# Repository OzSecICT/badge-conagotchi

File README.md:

# OzSec 2026: Conagotchi

Private repository for the OzSec 2026 Conagotchi badge — an ESP32-S3 interactive badge with a round GC9A01 display, virtual pet (Conagotchi) mode, and CTF challenge mode.

## Setup

Install host tools:

```bash
pip install esptool mpremote Pillow
```

## Flashing MicroPython firmware

```bash
esptool.py --chip esp32s3 --before default-reset --after hard-reset \
    write_flash -z 0x0 firmware/ESP32_GENERIC_S3-SPIRAM_OCT-20251209-v1.27.0.bin
```

## Deploying code

```bash
mpremote cp -r source/. :
mpremote reset
```

The VS Code default task (`Ctrl+Shift+B`) does both steps automatically.

## Converting images for the display

The GC9A01 display is 240×240 pixels round. Images must be converted from PNG to raw RGB565 binary before being copied to the badge — MicroPython cannot decode PNGs at runtime.

### Install the conversion tool dependency

```bash
pip install Pillow
```

### Full-screen backgrounds (240×240)

Design your PNG at 240×240 pixels. The corners outside the circular bezel are never shown, so no special treatment is needed — just design for a circle inscribed in the square.

```bash
python tools/convert_image.py your_image.png --outdir source/img
```

Produces `source/img/your_image.bin` — 115,200 bytes (240 × 240 × 2).

### Character animation frames

The Conagotchi idle animation uses sprite frames sized to the character bounding box (100×115 px by default). Export individual frames from your animation tool as transparent-background PNGs, then convert:

```bash
# Pre-sized PNGs (100×115) — convert without resizing
python tools/convert_image.py char_idle_0.png char_idle_1.png char_idle_2.png char_idle_3.png \
    --no-resize --outdir source/img

# OR crop from a full 240×240 mockup
python tools/convert_image.py mockup_frame0.png --crop 70,52,100,115 \
    --output source/img/char_idle_0.bin
```

The `--crop` coordinates (`x,y,w,h`) match the `_CHAR_X`, `_CHAR_Y`, `_CHAR_W`, `_CHAR_H` constants in `source/screens/conagotchi.py`.

### Menu button sprites

Each navigation button has three states: unselected (baked into the background), selected, and pressed. The selected/pressed states are small sprite files:

```bash
# Pre-sized sprite PNG
python tools/convert_image.py btn_pet_sel.png --no-resize --outdir source/img

# OR crop the button region from a full 240×240 state mockup
# Coordinates match the _BUTTONS table in source/screens/menu.py
python tools/convert_image.py menu_mockup_selected.png --crop 90,5,60,45 \
    --output source/img/btn_pet_sel.bin
```

### Compositing transparent overlays

If your overlay PNG has an alpha channel (transparency), composite it onto the background before converting:

```bash
python tools/convert_image.py background.png overlay.png \
    --composite --output source/img/result.bin
```

### Deploy images to badge

Images live in `source/img/` and are deployed alongside the Python files:

```bash
mpremote cp -r source/. :
```

### Expected image files

| File | Purpose |
|------|---------|
| `source/img/logo.bin` | Splash screen background |
| `source/img/{character}/background.bin` | Per-character main screen background (240×240) |
| `source/img/{character}/character.bin` | Idle animation base frame (80×80) |
| `source/img/{character}/idle_1.bin` … | Additional idle animation frames (optional) |
| `source/img/menu_bg.bin` | Menu screen background (all buttons unselected) |
| `source/img/btn_{id}_sel.bin` | Per-button selected state sprite |
| `source/img/btn_{id}_press.bin` | Per-button pressed state sprite |

The active character is set by `_CHARACTER` in `source/screens/conagotchi.py` (currently `"hackachi"`).

All `.bin` files are gitignored — generate them locally from your source PNGs.

## Hardware notes

- IR receiver to be changed to TSOP57438TT1 ([JLCPCB part](https://jlcpcb.com/partdetail/VishayIntertech-TSOP57438TT1/C3742825))

## Diagnostics

Run this on the REPL to check memory and flash:

```python
import gc, sys, esp32, os; gc.collect(); print(f"\n=== MicroPython Info ===\nImplementation: {sys.implementation}\nPlatform: {sys.platform}\nuname: {os.uname()}\n\n=== Memory ===\nFree: {gc.mem_free()/1024:.1f} KB\nUsed: {gc.mem_alloc()/1024:.1f} KB\nTotal: {(gc.mem_free()+gc.mem_alloc())/1024:.1f} KB\n\n=== Heap Regions ==="); [print(f"  {r[0]/1024/1024:.2f} MB total, {r[1]/1024/1024:.2f} MB free, {r[2]} largest block") for r in esp32.idf_heap_info(esp32.HEAP_DATA)]; print(f"\n=== Flash ==="); import esp; print(f"  Flash size: {esp.flash_size()/1024/1024:.0f} MB")
```

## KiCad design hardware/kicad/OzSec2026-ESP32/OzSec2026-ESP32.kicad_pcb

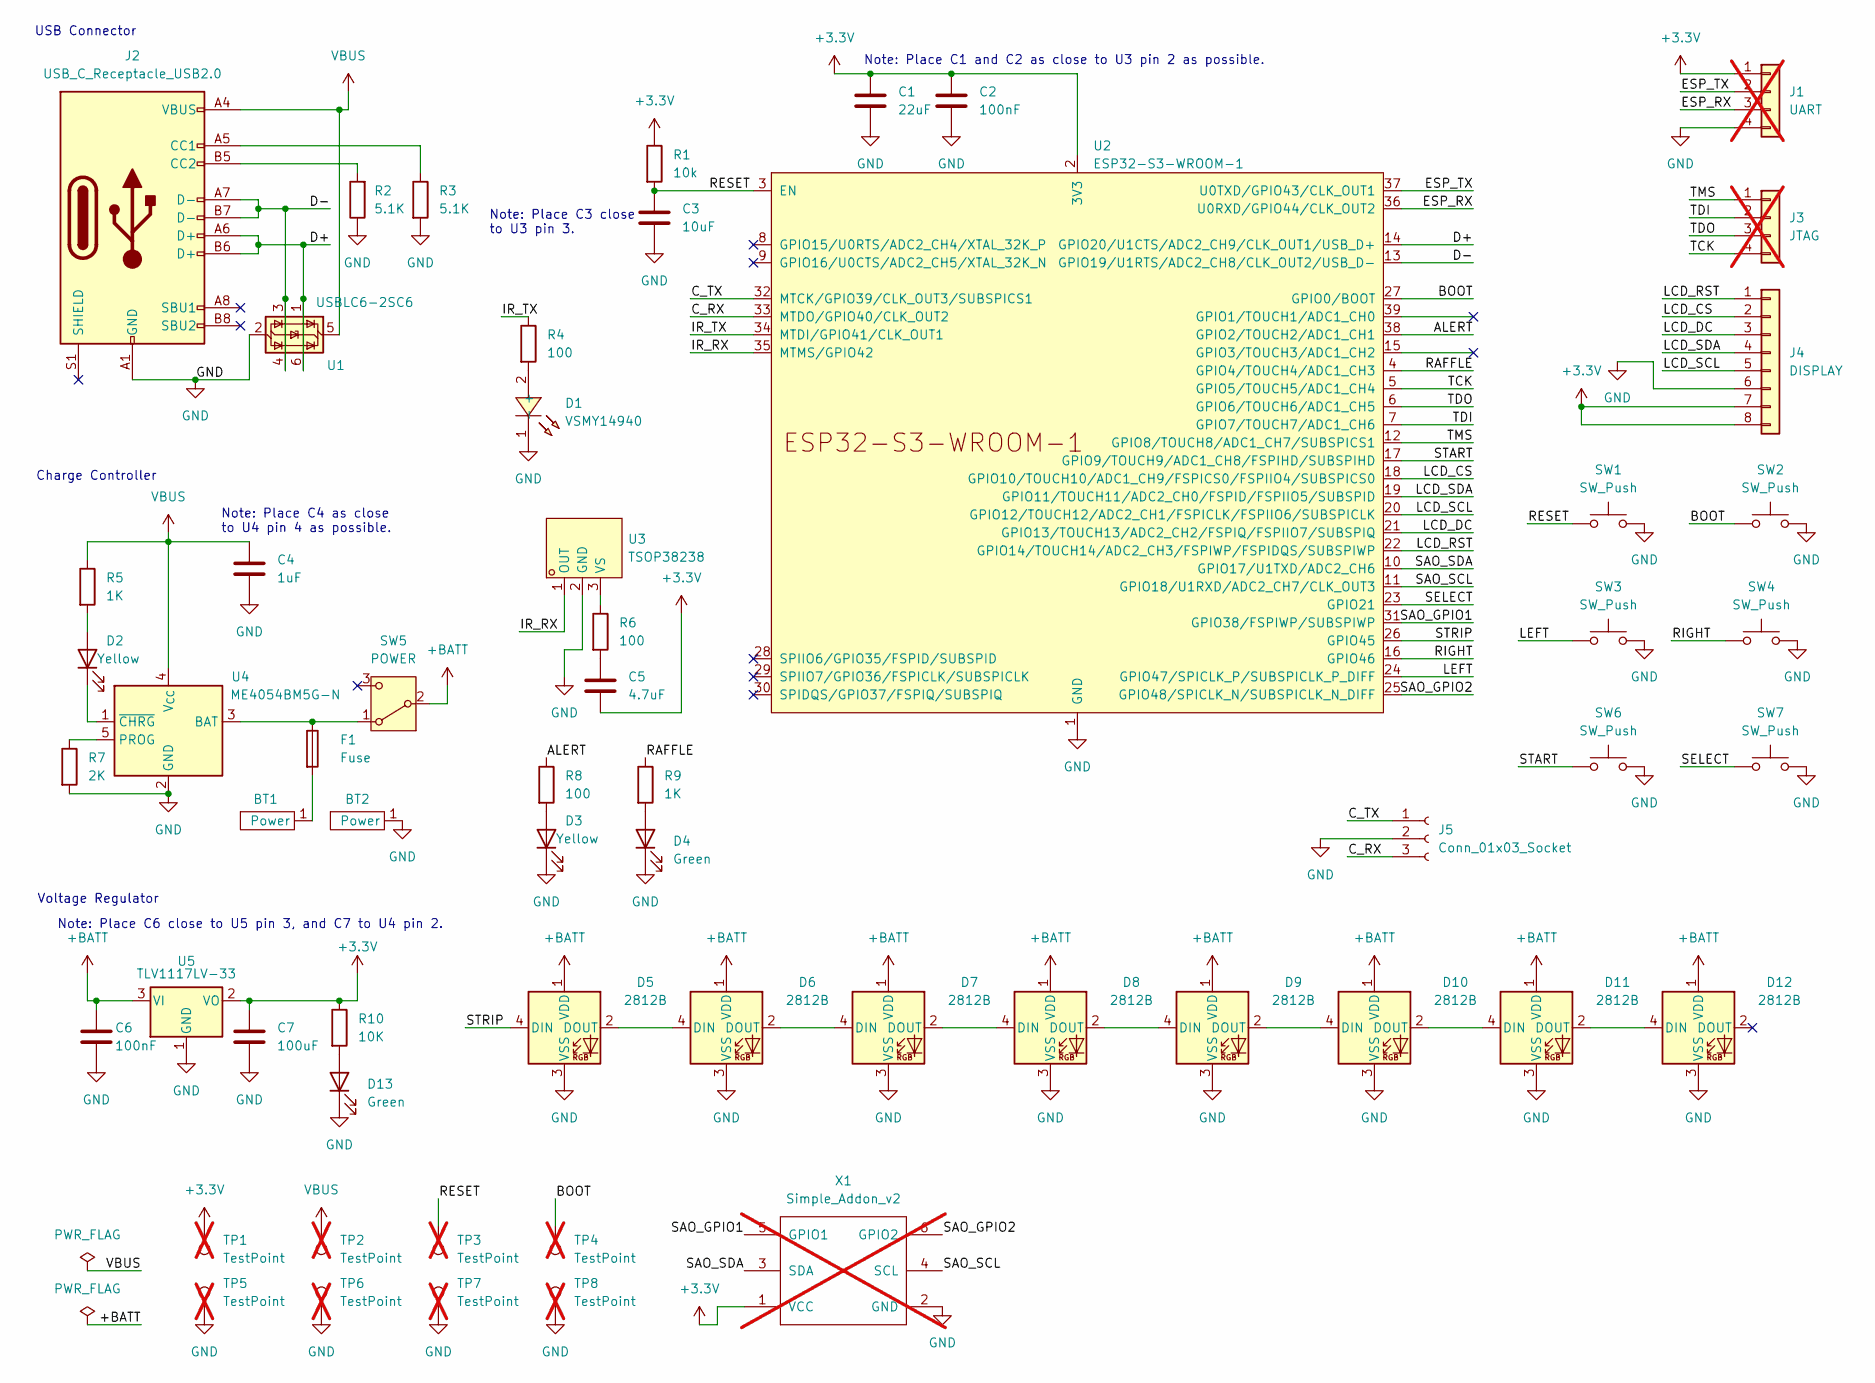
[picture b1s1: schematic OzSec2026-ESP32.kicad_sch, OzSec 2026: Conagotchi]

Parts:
BT1: MY-AA-04_BT1A; LCSC C2979179
BT2: MY-AA-04_BT1B; LCSC C2979179
C1: 22uF; C_0805_2012Metric; LCSC C45783
C2, C6: 100nF; C_0805_2012Metric; LCSC C49678
C3: 10uF; C_0805_2012Metric; LCSC C15850
C4: 1uF; C_0805_2012Metric; LCSC C28323
C5: 4.7uF; C_0805_2012Metric; LCSC C1779
C7: 100uF; C_1206_3216Metric; LCSC C15008
D1: VSMY14940; LED_MB14940_VIS; LCSC C511069
D2, D3: Yellow; D_0805_2012Metric; LCSC C2296
D4, D13: Green; D_0805_2012Metric; LCSC C2297
D5, D6, D7, D8, D9, D10, D11, D12: 2812B; D_SMD5050-4P_XL-5050RGBC-2812B; LCSC C2843785
F1: Fuse; Fuse_1206_3216Metric; LCSC C261957
J1: UART; PinHeader_1x04_P2.54mm_Vertical; not fitted
J2: USB_C_Receptacle_USB2.0; USB_C_Receptacle_G-Switch_GT-USB-7010ASV; LCSC C2988369
J3: JTAG; PinHeader_1x04_P2.54mm_Vertical; not fitted
J4: DISPLAY; PinSocket_1x08_P2.54mm_Vertical; LCSC C42431840
J5: Conn_01x03_Socket; PinHeader_1x03_P2.54mm_Horizontal; LCSC C492411
R1: 10k; R_0805_2012Metric; LCSC C17414
R2, R3: 5.1K; R_0805_2012Metric; LCSC C27834
R4, R6, R8: 100; R_0805_2012Metric; LCSC C17408
R5, R9: 1K; R_0805_2012Metric; LCSC C17513
R7: 2K; R_0805_2012Metric; LCSC C17604
R10: 10K; R_0805_2012Metric; LCSC C17414
SW1, SW2: SW_Push; SW_Push_1P1T_XKB_TS-1187A; LCSC C318884
SW3, SW4, SW6, SW7: SW_Push; SW-SMD_4P-L4.5-W4.5-P3.00-LS6.8; LCSC C2888900
SW5: POWER; SW_SPDT_PCM12; LCSC C431541
TP1, TP2, TP3, TP4: TestPoint; TestPoint_Pad_D1.5mm; not fitted
TP5, TP6, TP7, TP8: TestPoint; TestPoint_Pad_1.5x1.5mm; not fitted
U1: USBLC6-2SC6; SOT-23-6; LCSC C2827654
U2: ESP32-S3-WROOM-1; LCSC C2913201
U3: TSOP38238; TSOP382; LCSC Part C141632
U4: ME4054BM5G-N; TSOT-23-5; LCSC C478383
U5: TLV1117LV-33; TLV1117LV; LCSC C15578
X1: Simple_Addon_v2; Simple_Addon_v2-BADGE-2x3; LCSC C18164972; not fitted

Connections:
+3.3V: C1.1, C2.1, C5.2, C7.1, J1.1, J4.7, J4.8, R1.1, R10.1, TP1.1, U2.2 (3V3), U5.2 (VO), X1.1 (VCC)
+BATT: C6.1, D5.1 (VDD), D6.1 (VDD), D7.1 (VDD), D8.1 (VDD), D9.1 (VDD), D10.1 (VDD), D11.1 (VDD), D12.1 (VDD), SW5.2 (B), U5.3 (VI)
/ALERT: R8.1, U2.38 (GPIO2/TOUCH2/ADC1_CH1)
/BOOT: SW2.1, TP4.1, U2.27 (GPIO0/BOOT)
/C_RX: J5.3, U2.33 (MTDO/GPIO40/CLK_OUT2)
/C_TX: J5.1, U2.32 (MTCK/GPIO39/CLK_OUT3/SUBSPICS1)
/D+: J2.A6 (D+), J2.B6 (D+), U1.1 (I/O1), U1.6 (I/O1), U2.14 (GPIO20/U1CTS/ADC2_CH9/CLK_OUT1/USB_D+)
/D-: J2.A7 (D-), J2.B7 (D-), U1.3 (I/O2), U1.4 (I/O2), U2.13 (GPIO19/U1RTS/ADC2_CH8/CLK_OUT2/USB_D-)
/ESP_RX: J1.3, U2.36 (U0RXD/GPIO44/CLK_OUT2)
/ESP_TX: J1.2, U2.37 (U0TXD/GPIO43/CLK_OUT1)
/IR_RX: U2.35 (MTMS/GPIO42), U3.1 (OUT)
/IR_TX: R4.1, U2.34 (MTDI/GPIO41/CLK_OUT1)
/LCD_CS: J4.2, U2.18 (GPIO10/TOUCH10/ADC1_CH9/FSPICS0/FSPIIO4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)
/LCD_DC: J4.3, U2.21 (GPIO13/TOUCH13/ADC2_CH2/FSPIQ/FSPIIO7/S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)
/LCD_RST: J4.1, U2.22 (GPIO14/TOUCH14/ADC2_CH3/FSPIWP/FSPIDQS/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)
/LCD_SCL: J4.5, U2.20 (GPIO12/TOUCH12/ADC2_CH1/FSPICLK/FSPIIO6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)
/LCD_SDA: J4.4, U2.19 (GPIO11/TOUCH11/ADC2_CH0/FSPID/FSPIIO5/S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)
/LEFT: SW3.1, U2.24 (GPIO47/SPICLK_P/SUBSPICLK_P_DIFF)
/RAFFLE: R9.1, U2.4 (GPIO4/TOUCH4/ADC1_CH3)
/RESET: C3.1, R1.2, SW1.1, TP3.1, U2.3 (EN)
/RIGHT: SW4.1, U2.16 (GPIO46)
/SAO_GPIO1: U2.31 (GPIO38/FSPIWP/SUBSPIWP), X1.5 (GPIO1)
/SAO_GPIO2: U2.25 (GPIO48/SPICLK_N/SUBSPICLK_N_DIFF), X1.6 (GPIO2)
/SAO_SCL: U2.11 (GPIO18/U1RXD/ADC2_CH7/CLK_OUT3), X1.4 (SCL)
/SAO_SDA: U2.10 (GPIO17/U1TXD/ADC2_CH6), X1.3 (SDA)
/SELECT: SW7.1, U2.23 (GPIO21)
/START: SW6.1, U2.17 (GPIO9/TOUCH9/ADC1_CH8/FSPIHD/SUBSPIHD)
/STRIP: D5.4 (DIN), U2.26 (GPIO45)
/TCK: J3.4, U2.5 (GPIO5/TOUCH5/ADC1_CH4)
/TDI: J3.2, U2.7 (GPIO7/TOUCH7/ADC1_CH6)
/TDO: J3.3, U2.6 (GPIO6/TOUCH6/ADC1_CH5)
/TMS: J3.1, U2.12 (GPIO8/TOUCH8/ADC1_CH7/SUBSPICS1)
GND: BT2.1 (Power), C1.2, C2.2, C3.2, C4.2, C6.2, C7.2, D1.1 (-), D3.1 (K), D4.1 (K), D5.3 (VSS), D6.3 (VSS), D7.3 (VSS), D8.3 (VSS), D9.3 (VSS), D10.3 (VSS), D11.3 (VSS), D12.3 (VSS), D13.1 (K), J1.4, J2.A1 (GND), J2.A12 (GND), J2.B1 (GND), J2.B12 (GND), J4.6, J5.2, R2.1, R3.2, R7.2, SW1.2, SW2.2, SW3.2, SW4.2, SW6.2, SW7.2, TP5.1, TP6.1, TP7.1, TP8.1, U1.2 (GND), U2.1 (GND), U2.40 (GND), U2.41 (GND), U3.2 (GND), U4.2 (GND), U5.1 (GND), X1.2 (GND)
unnamed 33: BT1.1, F1.2; also elsewhere on the board
unnamed: C5.1, R6.2
unnamed: D1.2 (+), R4.2
unnamed: D2.2 (A), R5.2
unnamed: D2.1 (K), U4.1 (~CHRG)
unnamed: D3.2 (A), R8.2
unnamed: D4.2 (A), R9.2
unnamed: D5.2 (DOUT), D6.4 (DIN)
unnamed: D6.2 (DOUT), D7.4 (DIN)
unnamed: D7.2 (DOUT), D8.4 (DIN)
unnamed: D8.2 (DOUT), D9.4 (DIN)
unnamed: D9.2 (DOUT), D10.4 (DIN)
unnamed: D10.2 (DOUT), D11.4 (DIN)
unnamed: D11.2 (DOUT), D12.4 (DIN)
unnamed: D13.2 (A), R10.2
unnamed: J2.A5 (CC1), R3.1
unnamed: J2.B5 (CC2), R2.2
unnamed: F1.1, SW5.1 (A), U4.3 (BAT)
unnamed: R6.1, U3.3 (VS)
unnamed: R7.1, U4.5 (PROG)
VBUS: C4.1, J2.A4 (VBUS), J2.A9 (VBUS), J2.B4 (VBUS), J2.B9 (VBUS), R5.1, TP2.1, U1.5 (VBUS), U4.4 (V_{CC})

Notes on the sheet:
Note: Place C3 close to U3 pin 3.
USB Connector
Note: Place C6 close to U5 pin 3, and C7 to U4 pin 2.
Voltage Regulator
Note: Place C4 as close to U4 pin 4 as possible.
Charge Controller
Note: Place C1 and C2 as close to U3 pin 2 as possible.

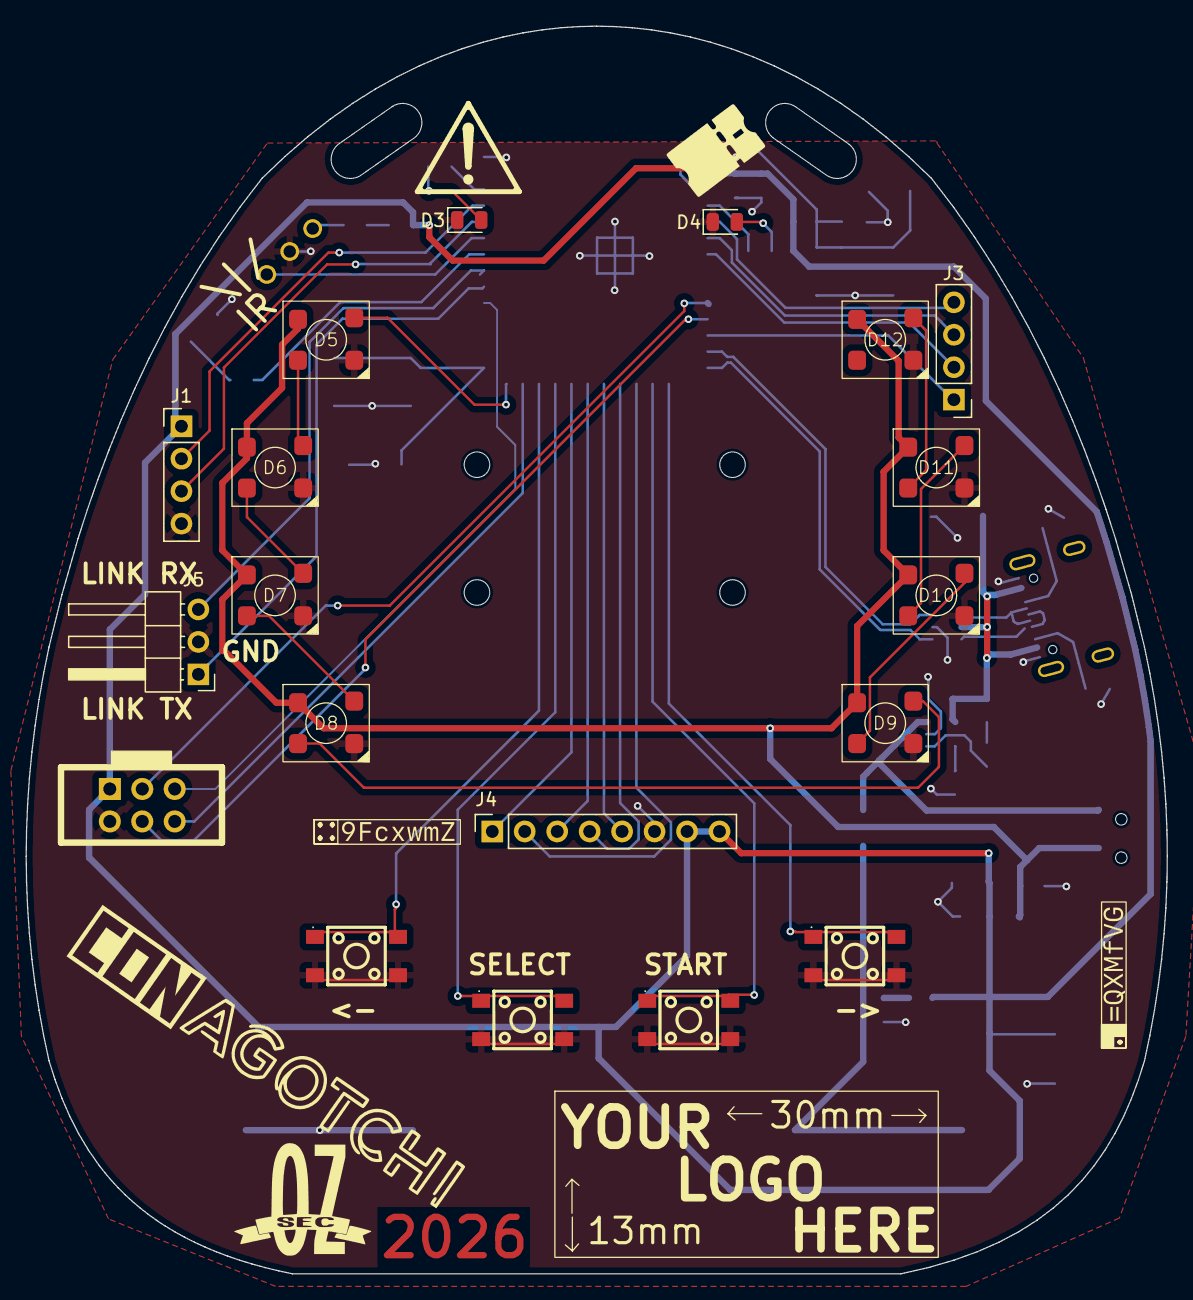
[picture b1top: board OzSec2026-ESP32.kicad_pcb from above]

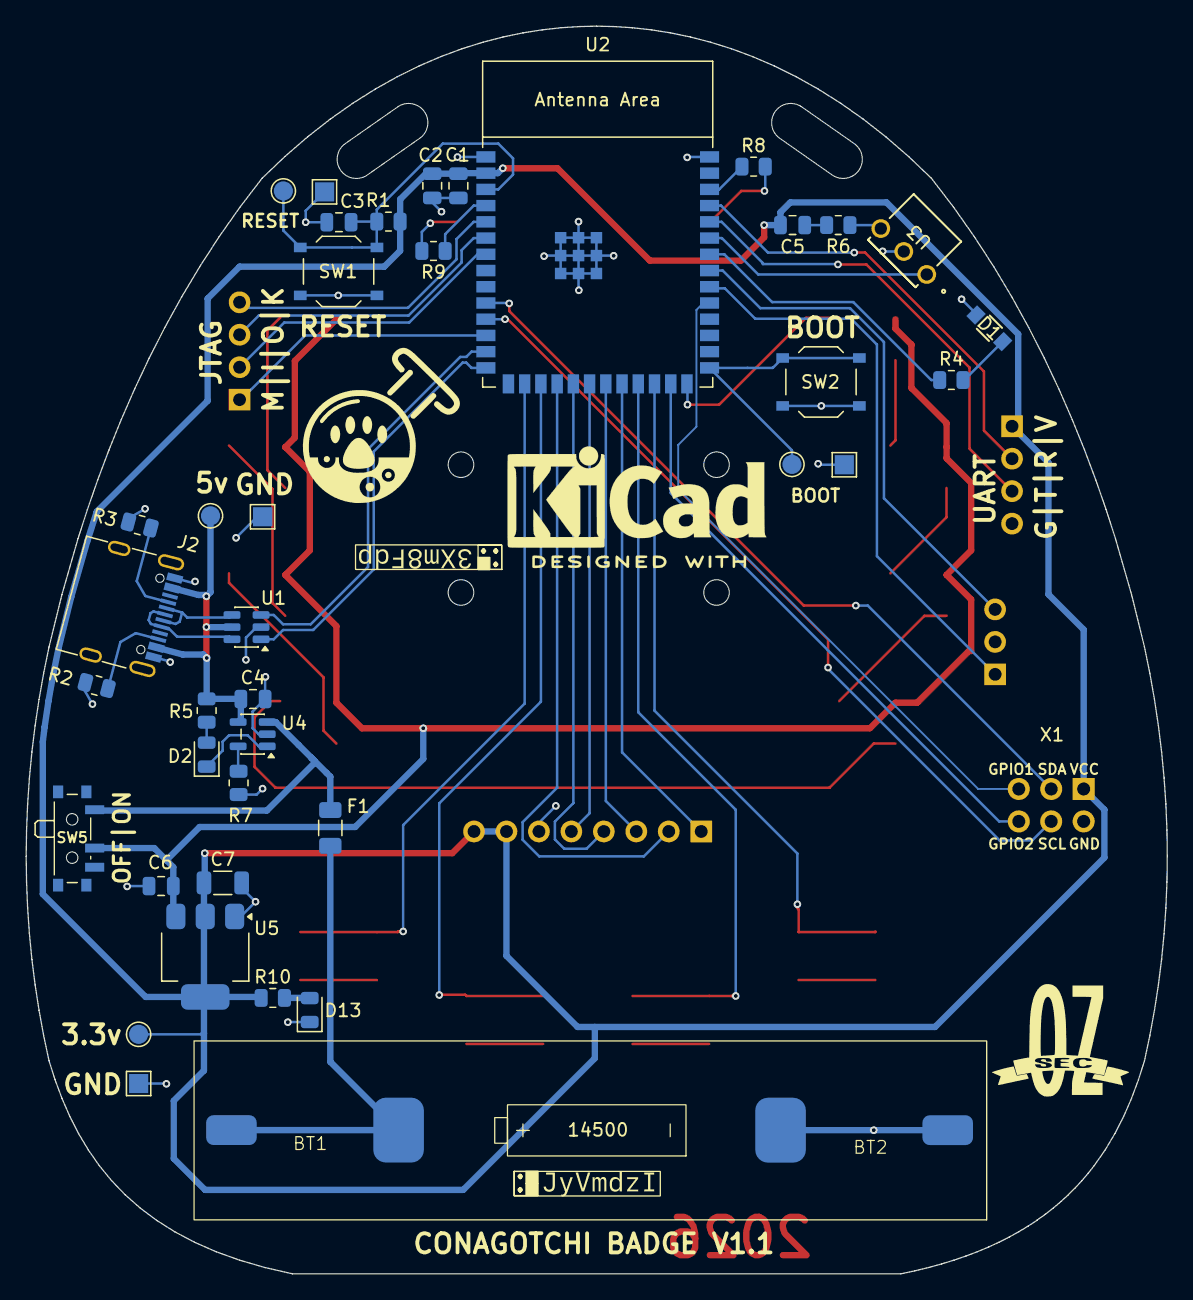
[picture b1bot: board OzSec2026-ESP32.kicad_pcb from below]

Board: 2 copper layers, 89.3 x 97.6 mm, 60 parts (41 on the bottom side), 54 nets.

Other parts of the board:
BT1#2: MY-AA-04_BT1A

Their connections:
unnamed 33: BT1#2.1 (Power); also elsewhere on the board

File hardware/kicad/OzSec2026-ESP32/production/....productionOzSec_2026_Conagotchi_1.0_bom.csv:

Designator,Footprint,Quantity,Value,LCSC Part #
BT1_2,MY-AA-04_Silkscreen_Only,1,Battery,C2979179
BT1,MY-AA-04_BT1A,1,~,C2979179
BT2,MY-AA-04_BT1B,1,~,C2979179
C1,0805,1,22uF,C45783
"C2, C6",0805,2,100nF,C49678
C3,0805,1,10uF,C15850
C4,0805,1,1uF,C28323
C5,0805,1,4.7uF,C1779
C7,1206,1,100uF,C15008
"D1, D2",0805,2,Yellow,C2296
"D10, D11, D4, D5, D6, D7, D8, D9",D_SMD5050-4P_XL-5050RGBC-2812B,8,2812B,C2843785
"D12, D3",0805,2,Green,C2297
F1,1206,1,Fuse,C261957
J2,USB_C_Receptacle_G-Switch_GT-USB-7010ASV,1,USB_C_Receptacle_USB2.0,C2988369
J4,PinSocket_1x08_P2.54mm_Vertical,1,DISPLAY,C42431840
J5,PinHeader_1x03_P2.54mm_Horizontal,1,Conn_01x03_Socket,C492411
LED1,TSOP382,1,TSOP38238,C141632
R1,0805,1,10k,C17414
"R10, R7",0805,2,2K,C17604
"R2, R3",0805,2,5.1K,C27834
"R4, R6",0805,2,100,C17408
"R5, R8, R9",0805,3,1K,C17513
"SW1, SW2, SW3, SW4, SW6, SW7",SW_Push_1P1T_XKB_TS-1187A,6,SW_Push,
SW5,SW_SPDT_PCM12,1,POWER,C431541
U1,SOT-23-6,1,USBLC6-2SC6,C2827654
U2,LED_MB14940_VIS,1,VSMY14940,C511069
U3,ESP32-S3-WROOM-1,1,ESP32-S3-WROOM-1,C2913201
U4,TSOT-23-5,1,ME4054BM5G-N,C478383
U5,TLV1117LV,1,TLV1117LV-33,C15578

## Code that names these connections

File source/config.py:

# Badge hardware pin assignments and tunable constants.
# Import this everywhere rather than hard-coding pin numbers.

# ── UART ──────────────────────────────────────────────────────────────────────
PIN_UART_TX         = 43
PIN_UART_RX         = 44

# ── I2C (SAO connector) ───────────────────────────────────────────────────────
PIN_I2C_SDA         = 17
PIN_I2C_SCL         = 18

# ── Buttons (active-low, internal pull-up) ────────────────────────────────────
PIN_BTN_BOOT        = 0
PIN_BTN_START       = 9
PIN_BTN_SELECT      = 21
PIN_BTN_RIGHT       = 46
PIN_BTN_LEFT        = 47
DEBOUNCE_MS         = 100

# ── SAO expansion GPIOs ───────────────────────────────────────────────────────
PIN_SAO_GPIO1       = 38
PIN_SAO_GPIO2       = 48

# ── LEDs ──────────────────────────────────────────────────────────────────────
PIN_LED_ALERT       = 2     # Red indicator — character needs attention
PIN_LED_RAFFLE      = 4     # Green indicator — raffle ticket earned
PIN_LED_RGB         = 45    # WS2812B data line
NUM_RGB_LEDS        = 8

# ── Display — GC9A01 240×240 round, SPI ──────────────────────────────────────
PIN_DISP_CS         = 10
PIN_DISP_MOSI       = 11    # Labelled SDA on display silkscreen
PIN_DISP_SCK        = 12    # Labelled SCL on display silkscreen
PIN_DISP_DC         = 13
PIN_DISP_RST        = 14
DISP_WIDTH          = 240
DISP_HEIGHT         = 240
DISP_SPI_FREQ       = 40_000_000

# ── IR badge-to-badge link ────────────────────────────────────────────────────
PIN_IR_TX           = 41
PIN_IR_RX           = 42
IR_FREQ_HZ          = 38_000   # matches TSOP38238 receiver

# ── Wired badge-to-badge link ─────────────────────────────────────────────────
PIN_LINK_TX         = 39
PIN_LINK_RX         = 40
LINK_BAUD           = 115200

# ── WiFi ──────────────────────────────────────────────────────────────────────
WIFI_SSID           = "OzSec 2026"
WIFI_PASSWORD       = "OzSec2026WiFi!"
WIFI_TIMEOUT_S      = 10

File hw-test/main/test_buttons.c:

#include <stdbool.h>
#include "freertos/FreeRTOS.h"
#include "freertos/task.h"
#include "driver/gpio.h"
#include "esp_log.h"
#include "esp_timer.h"
#include "display.h"
#include "ws2812.h"
#include "badge_hw.h"
#include "test_buttons.h"

static const char *TAG = "button_test";

/*
 * Circular display safe-zone layout (circle r=120, center 120,120):
 *
 *  y=50  "BUTTON TEST"  scale 2, 11 chars*12=132px, x=54..186
 *        corner (54,50): dist≈94 — safe
 *  y=71  hline x=35..205
 *        corner (35,71): dist≈101 — safe
 *  Rows y=87,109,131,153,175  (5 buttons, 22px apart)
 *        at y=175 (dist=55 from cy): safe x = 120±107 → 13..227
 *        left dot x=20, right dot x=210 both verified safe
 *  y=197 hline x=35..205
 *        corner (35,197): dist≈101 — safe
 *  y=207 footer scale 1, centered — safe
 */

typedef enum {
    PHASE_TESTING,   /* tracking first-press of each button */
    PHASE_ALL_DONE,  /* all buttons seen; waiting for BOOT hold */
    PHASE_LEDS_ON,   /* all LEDs lit; waiting for BOOT press to restart */
} phase_t;

typedef struct {
    const char  *label;
    gpio_num_t   pin;
} btn_def_t;

static const btn_def_t BTNS[] = {
    {"BOOT  GPIO0",  BTN_BOOT_PIN   },
    {"START GPIO9",  BTN_START_PIN  },
    {"SEL  GPIO21",  BTN_SELECT_PIN },
    {"RGHT GPIO46",  BTN_RIGHT_PIN  },
    {"LEFT GPIO47",  BTN_LEFT_PIN   },
};
#define BTN_COUNT 5

static const int ROW_Y[BTN_COUNT] = { 87, 109, 131, 153, 175 };

/* Draw the static background (called once and on restart) */
static void draw_static(void)
{
    display_fill(COLOR_BLACK);
    display_draw_string_center(50, "BUTTON TEST", COLOR_WHITE, COLOR_BLACK, 2);
    display_draw_hline(35, 71, 170, COLOR_GRAY);

    for (int i = 0; i < BTN_COUNT; i++)
        display_draw_string_center(ROW_Y[i], BTNS[i].label, COLOR_DARKGRAY, COLOR_BLACK, 1);

    display_draw_hline(35, 197, 170, COLOR_GRAY);
    display_draw_string_center(207, "Press all buttons!", COLOR_GRAY, COLOR_BLACK, 1);
}

/* Update a single row's indicator dots and label color */
static void update_row(int i, bool pressed)
{
    uint16_t color = pressed ? COLOR_GREEN : COLOR_DARKGRAY;
    display_fill_rect(20,  ROW_Y[i], 9, 9, color);
    display_fill_rect(211, ROW_Y[i], 9, 9, color);
    display_draw_string_center(ROW_Y[i], BTNS[i].label, color, COLOR_BLACK, 1);
}

/* Replace only the footer text, leaving the hline intact */
static void update_footer(const char *text, uint16_t color)
{
    display_fill_rect(0, 198, 240, 28, COLOR_BLACK);
    display_draw_string_center(207, text, color, COLOR_BLACK, 1);
}

static void draw_celebration(void)
{
    display_fill(COLOR_BLACK);
    display_fill_circle(120, 120, 108, COLOR_DARKGRAY);
    display_draw_string_center(92,  "ALL LEDS ON!", COLOR_GREEN,  COLOR_DARKGRAY, 2);
    display_draw_hline(55, 120, 110, COLOR_GRAY);
    display_draw_string_center(133, "Press BOOT",  COLOR_YELLOW, COLOR_DARKGRAY, 1);
    display_draw_string_center(145, "to restart",  COLOR_YELLOW, COLOR_DARKGRAY, 1);
}

void test_buttons_run(void)
{
    draw_static();

    bool     prev[BTN_COUNT]         = {false};
    bool     ever_pressed[BTN_COUNT] = {false};
    int      pressed_count           = 0;
    phase_t  phase                   = PHASE_TESTING;

    ESP_LOGI(TAG, "Button test started — press all %d buttons to unlock", BTN_COUNT);

    while (1) {

        /* ── Normal button tracking (BOOT skipped in non-testing phases) ── */
        for (int i = 0; i < BTN_COUNT; i++) {
            if (phase != PHASE_TESTING && i == 0) continue;

            bool pressed = (gpio_get_level(BTNS[i].pin) == 0);
            if (pressed != prev[i]) {
                prev[i] = pressed;

                if (pressed && !ever_pressed[i]) {
                    ever_pressed[i] = true;
                    pressed_count++;
                    ESP_LOGI(TAG, "%-14s (GPIO%2d): PRESSED  [%d/%d]",
                             BTNS[i].label, BTNS[i].pin, pressed_count, BTN_COUNT);
                } else {
                    ESP_LOGI(TAG, "%-14s (GPIO%2d): %s",
                             BTNS[i].label, BTNS[i].pin, pressed ? "PRESSED" : "released");
                }
                update_row(i, pressed);
            }
        }

        /* ── Transition: all buttons pressed for the first time ── */
        if (phase == PHASE_TESTING && pressed_count == BTN_COUNT) {
            phase = PHASE_ALL_DONE;
            ESP_LOGI(TAG, "All buttons pressed! Hold BOOT to activate all LEDs");
            update_footer("Hold BOOT to unlock!", COLOR_YELLOW);
        }

        /* ── PHASE_ALL_DONE: detect BOOT held ≥500ms ── */
        if (phase == PHASE_ALL_DONE && gpio_get_level(BTN_BOOT_PIN) == 0) {
            uint64_t t0 = esp_timer_get_time();
            while (gpio_get_level(BTN_BOOT_PIN) == 0) {
                vTaskDelay(pdMS_TO_TICKS(10));
                if ((esp_timer_get_time() - t0) >= 500000ULL) {
                    /* Held long enough — light everything */
                    gpio_set_level(LED_ALERT_PIN,  1);
                    gpio_set_level(LED_RAFFLE_PIN, 1);
                    ws2812_set_all(255, 255, 255);
                    ws2812_show();
                    phase = PHASE_LEDS_ON;
                    ESP_LOGI(TAG, "BOOT held — all LEDs on. Press BOOT to restart.");
                    draw_celebration();
                    /* Wait for release so we don't immediately re-trigger */
                    while (gpio_get_level(BTN_BOOT_PIN) == 0)
                        vTaskDelay(pdMS_TO_TICKS(10));
                    break;
                }
            }
            /* If loop exited without hitting 500ms, it was a short press — ignore */
        }

        /* ── PHASE_LEDS_ON: any BOOT press restarts the full test ── */
        if (phase == PHASE_LEDS_ON && gpio_get_level(BTN_BOOT_PIN) == 0) {
            /* Debounce */
            vTaskDelay(pdMS_TO_TICKS(30));
            if (gpio_get_level(BTN_BOOT_PIN) == 0) {
                while (gpio_get_level(BTN_BOOT_PIN) == 0)
                    vTaskDelay(pdMS_TO_TICKS(10));
                /* Clean up and signal restart */
                gpio_set_level(LED_ALERT_PIN,  0);
                gpio_set_level(LED_RAFFLE_PIN, 0);
                ws2812_clear();
                ws2812_show();
                ESP_LOGI(TAG, "Restarting test sequence...");
                return;
            }
        }

        vTaskDelay(pdMS_TO_TICKS(20));
    }
}

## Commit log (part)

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2024-10-21 PIO project init.
2024-10-25 Test code for sample LCD display.
2025-06-21 Created repo
2025-06-21 Initial supporting files.
2025-06-21 Initial file structure
2026-03-29 Converting to MicroPython
2026-03-29 Add KiCad project
2026-03-29 Add MicroPython typings to allow for proper linting.
2026-03-29 Added render.py to generate pcb color options.
2026-03-29 Added datasheets for components.
2026-03-29 Added art and skeleton mpy files
2026-03-30 Fabrication files for prototype 1.
2026-03-30 Skeleton files and firmware
2026-03-30 Added silkscreen to LINK connector.
2026-05-07 Version 1.1 of PCB and some initial source files.
2026-05-09 Updating.
2026-05-09 Update gitignore
2026-05-10 Update gitignore for pycache
2026-05-10 Fixed tasks on macOS
2026-05-10 Updated debounce on buttons
2026-05-10 Typings stuff
2026-05-10 Working background and character idle display.
2026-05-10 Add background and character
